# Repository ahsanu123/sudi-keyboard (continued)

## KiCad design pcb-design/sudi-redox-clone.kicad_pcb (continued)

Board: 2 copper layers, 145 parts (3 on the bottom side), 93 nets, no tracks yet.

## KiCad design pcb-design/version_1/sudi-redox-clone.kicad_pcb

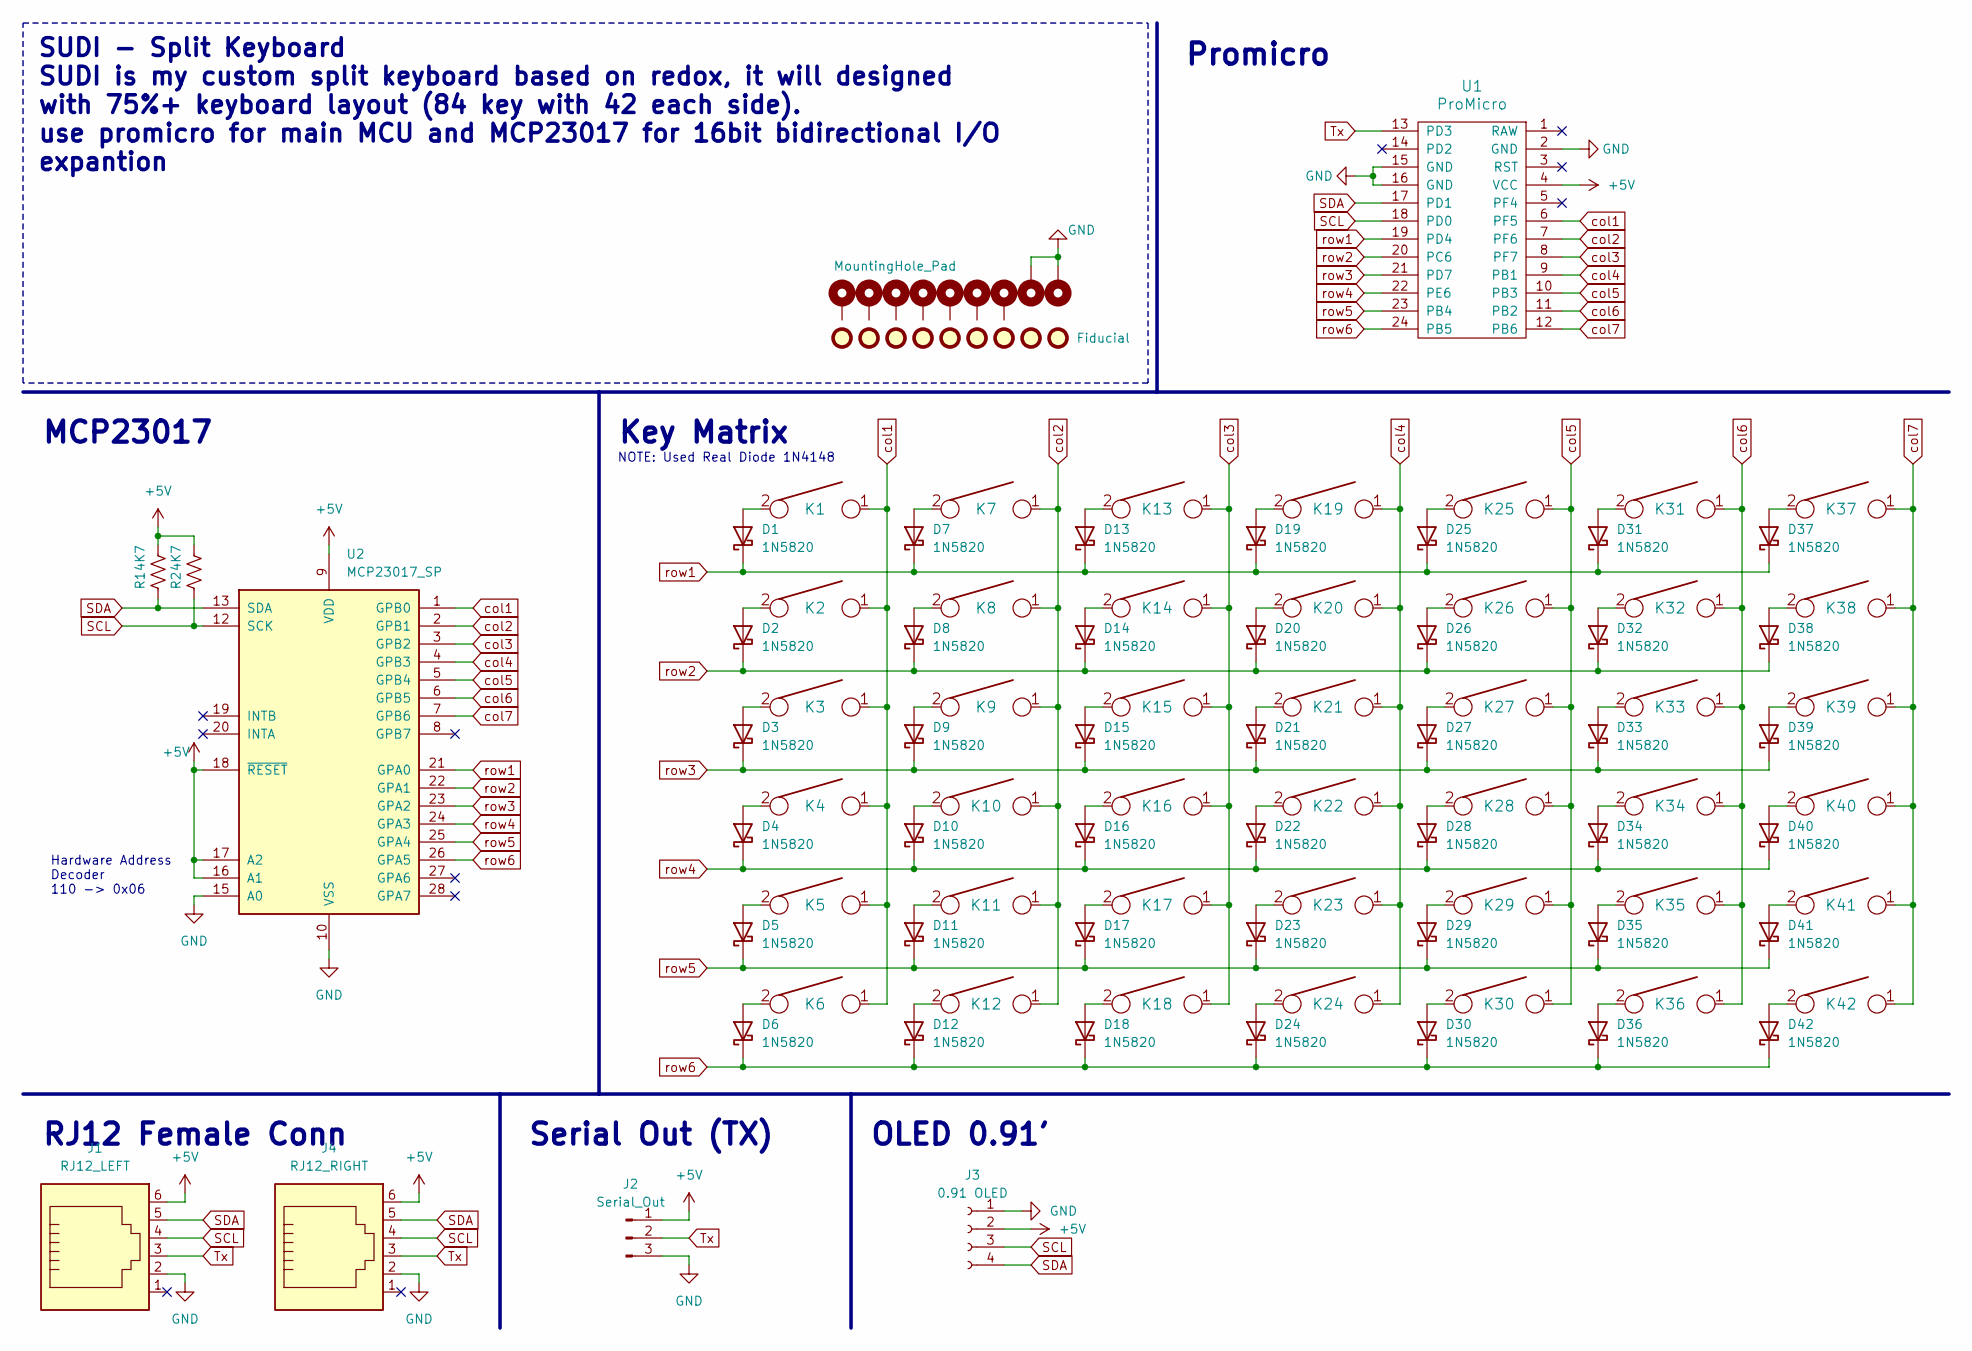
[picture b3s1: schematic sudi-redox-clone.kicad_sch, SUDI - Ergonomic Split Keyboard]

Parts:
D1, D2, D3, D4, D5, D6, D7, D8, D9, D10, D11, D12, D13, D14, D15, D16, D17, D18, D19, D20, D21, D22, D23, D24, D25, D26, D27, D28, D29, D30, D31, D32, D33, D34, D35, D36, D37, D38, D39, D40, D41, D42: 1N5820; D_SOD123_axial-dual
FID1, FID2, FID3, FID4, FID5, FID6, FID7, FID8, FID9: Fiducial; Fiducial_1mm_Mask3mm
H1, H2, H3, H4, H5, H6, H7, H8, H9: MountingHole_Pad; MountingHole_3.2mm_M3_DIN965_Pad
J1: RJ12_LEFT; RJ12_Amphenol_54601
J2: Serial_Out; PinHeader_1x03_P2.54mm_Horizontal
J3: 0.91 OLED; SSD1306-0.91-OLED-4pin-128x32
J4: RJ12_RIGHT; RJ12_Amphenol_54601
K1, K5, K6, K7, K8, K9, K10, K11, K12, K13, K14, K15, K16, K17, K18, K19, K20, K21, K22, K23, K24, K25, K26, K27, K28, K29, K30, K31, K32, K33, K34, K35, K36, K37, K38, K39, K40, K41, K42: KEYSW; Mx_Alps_100-dualside
K2, K3, K4: KEYSW; Mx_Alps_150-dualsided
R1, R2: 4K7; R_1206_3216Metric
U1: ProMicro; Pro_Micro
U2: MCP23017_SP; DIP-28_W7.62mm

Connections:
+5V: J1.6, J2.1, J3.2, J4.6, R1.1, R2.1, U1.4 (VCC), U2.9 (VDD), U2.16 (A1), U2.17 (A2), U2.18 (~RESET)
GND: H2.1, H9.1, J1.2, J2.3, J3.1, J4.2, U1.2 (GND), U1.15 (GND), U1.16 (GND), U2.10 (VSS), U2.15 (A0)
unnamed: D1.2 (A), K1.2
unnamed: D2.2 (A), K2.2
unnamed: D3.2 (A), K3.2
unnamed: D4.2 (A), K4.2
unnamed: D5.2 (A), K5.2
unnamed: D6.2 (A), K6.2
unnamed: D7.2 (A), K7.2
unnamed: D8.2 (A), K8.2
unnamed: D9.2 (A), K9.2
unnamed: D10.2 (A), K10.2
unnamed: D11.2 (A), K11.2
unnamed: D12.2 (A), K12.2
unnamed: D13.2 (A), K13.2
unnamed: D14.2 (A), K14.2
unnamed: D15.2 (A), K15.2
unnamed: D16.2 (A), K16.2
unnamed: D17.2 (A), K17.2
unnamed: D18.2 (A), K18.2
unnamed: D19.2 (A), K19.2
unnamed: D20.2 (A), K20.2
unnamed: D21.2 (A), K21.2
unnamed: D22.2 (A), K22.2
unnamed: D23.2 (A), K23.2
unnamed: D24.2 (A), K24.2
unnamed: D25.2 (A), K25.2
unnamed: D26.2 (A), K26.2
unnamed: D27.2 (A), K27.2
unnamed: D28.2 (A), K28.2
unnamed: D29.2 (A), K29.2
unnamed: D30.2 (A), K30.2
unnamed: D31.2 (A), K31.2
unnamed: D32.2 (A), K32.2
unnamed: D33.2 (A), K33.2
unnamed: D34.2 (A), K34.2
unnamed: D35.2 (A), K35.2
unnamed: D36.2 (A), K36.2
unnamed: D37.2 (A), K37.2
unnamed: D38.2 (A), K38.2
unnamed: D39.2 (A), K39.2
unnamed: D40.2 (A), K40.2
unnamed: D41.2 (A), K41.2
unnamed: D42.2 (A), K42.2
SCL: J1.4, J3.3, J4.4, R2.2, U1.18 (PD0), U2.12 (SCK)
SDA: J1.5, J3.4, J4.5, R1.2, U1.17 (PD1), U2.13 (SDA)
Tx: J1.3, J2.2, J4.3, U1.13 (PD3)
col1: K1.1, K2.1, K3.1, K4.1, K5.1, K6.1, U1.6 (PF5), U2.1 (GPB0)
col2: K7.1, K8.1, K9.1, K10.1, K11.1, K12.1, U1.7 (PF6), U2.2 (GPB1)
col3: K13.1, K14.1, K15.1, K16.1, K17.1, K18.1, U1.8 (PF7), U2.3 (GPB2)
col4: K19.1, K20.1, K21.1, K22.1, K23.1, K24.1, U1.9 (PB1), U2.4 (GPB3)
col5: K25.1, K26.1, K27.1, K28.1, K29.1, K30.1, U1.10 (PB3), U2.5 (GPB4)
col6: K31.1, K32.1, K33.1, K34.1, K35.1, K36.1, U1.11 (PB2), U2.6 (GPB5)
col7: K37.1, K38.1, K39.1, K40.1, K41.1, K42.1, U1.12 (PB6), U2.7 (GPB6)
row1: D1.1 (K), D7.1 (K), D13.1 (K), D19.1 (K), D25.1 (K), D31.1 (K), D37.1 (K), U1.19 (PD4), U2.21 (GPA0)
row2: D2.1 (K), D8.1 (K), D14.1 (K), D20.1 (K), D26.1 (K), D32.1 (K), D38.1 (K), U1.20 (PC6), U2.22 (GPA1)
row3: D3.1 (K), D9.1 (K), D15.1 (K), D21.1 (K), D27.1 (K), D33.1 (K), D39.1 (K), U1.21 (PD7), U2.23 (GPA2)
row4: D4.1 (K), D10.1 (K), D16.1 (K), D22.1 (K), D28.1 (K), D34.1 (K), D40.1 (K), U1.22 (PE6), U2.24 (GPA3)
row5: D5.1 (K), D11.1 (K), D17.1 (K), D23.1 (K), D29.1 (K), D35.1 (K), D41.1 (K), U1.23 (PB4), U2.25 (GPA4)
row6: D6.1 (K), D12.1 (K), D18.1 (K), D24.1 (K), D30.1 (K), D36.1 (K), D42.1 (K), U1.24 (PB5), U2.26 (GPA5)

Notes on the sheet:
SUDI - Split Keyboard SUDI is my custom split keyboard based on redox, it will designed with 75%+ keyboard layout (84 key with 42 each side). use promicro for main MCU and MCP23017 for 16bit bidirectional I/O expantion
Key Matrix
NOTE: Used Real Diode 1N4148
Serial Out (TX)
Hardware Address Decoder 110 -> 0x06
RJ12 Female Conn
OLED 0.91'
MCP23017
Promicro

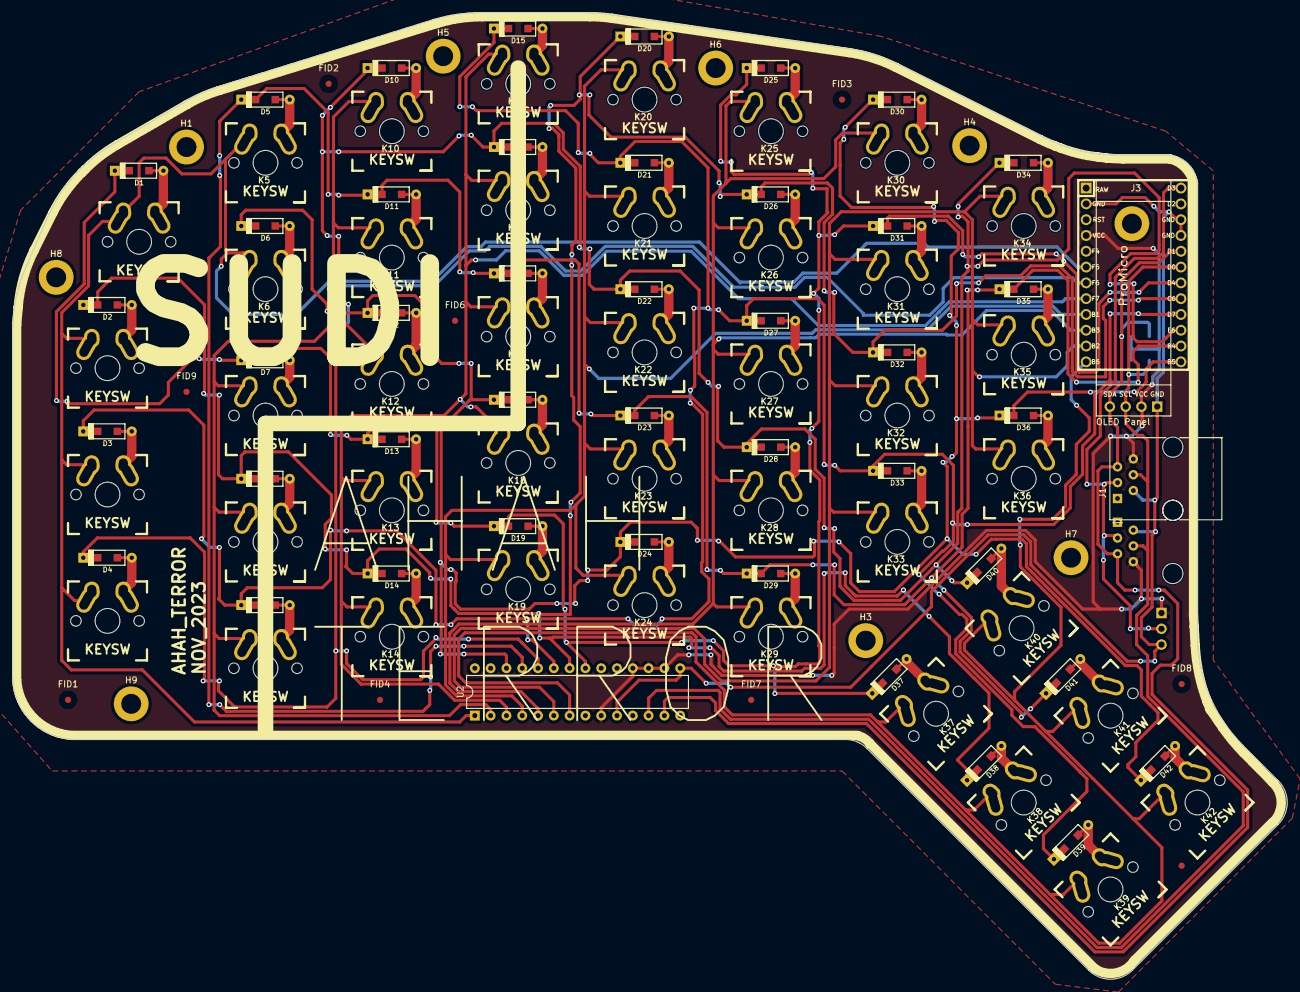
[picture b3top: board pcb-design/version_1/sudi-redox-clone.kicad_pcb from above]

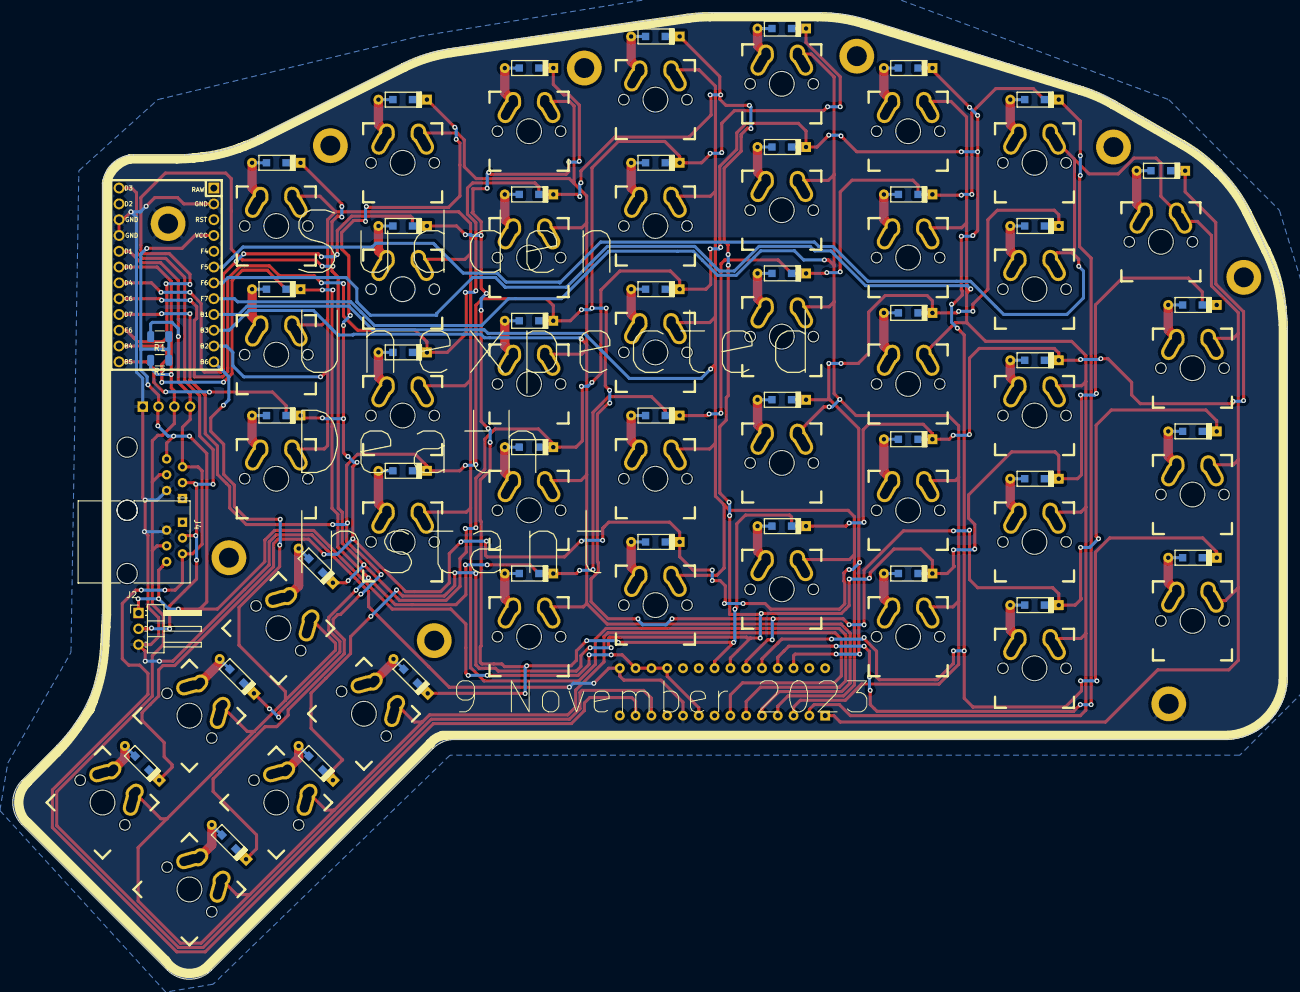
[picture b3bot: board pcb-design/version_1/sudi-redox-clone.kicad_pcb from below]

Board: 2 copper layers, 204.9 x 155.4 mm, 110 parts (4 on the bottom side), 60 nets.

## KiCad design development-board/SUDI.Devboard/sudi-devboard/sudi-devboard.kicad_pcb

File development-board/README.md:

## SUDI Development Board

Development board intended to understanding NRF52 nordic series for wireless keyboard, 
with Battery Management System (BMS), Bluetooth Low Energy Communication, USB, Vsense and 
LED Matrix.

## Description 

initial design decision, 

- NRF52820(5v tolerant, and USB, 256 kB flash, 32 kB RAM, QFN-40-EP(5x5), $2.6)
- NRF52832(**No** 5v tolerant, and **No** USB, 512/256 kB flash, 64/32 kB RAM, QFN-48-EP(6x6), $2.75)
- NRF52833QDXX(5v tolerant, and USB, 512 kB flash, 128 kB RAM, QFN-40-EP(5x5), $3.59)
- NRF52840(5v tolerant, and USB, 1 MB flash, 256 kB RAM, WLCSP-94(3.5x3.6) More difficult to Solder but most complete feature, $5.22)
- Add BMS into board 
- add IO expander, use MCP23017 smd
- board able to drive ws2812b (min voltage 3.5)
- vsense ic MAX17048
- switch to test 
- led for indicator 
- give all pin connector 
- usb with protection 
- uart 
- i2c 

## Note 

- [NRF51822 bluetooth module pin](https://quartzcomponents.com/cdn/shop/products/NRF51822-BLE-Module_1200x1200.jpg?v=1653290384)
  
```schell
left (from top perspectife, count from bottom)      Right (from top perspectife, count from bottom)  
PO3                                                 PO105                                            
PO4                                                 PO106                                            
PO1                                                 PO107                                            
PO2                                                 PO108                                            
PO30                                                PO109                                            
PO0                                                 PO110                                            
VDD                                                 PO111                                            
GND                                                 PO112                                            
PO28                                                PO003                                            
PO29                                                PO114                                            
NC                                                  PO015                                            
NC                                                  PO116                                            
PO24                                                SDA                                              
PO25                                                SCLK                                             
PO22                                                PO117                                            
PO23                                                PO119                                            
GND                                                 PO118                                            
PO21                                                PO200                                            

```

## Reference 

- [ebastler/zmk-designguide](https://github.com/ebastler/zmk-designguide)

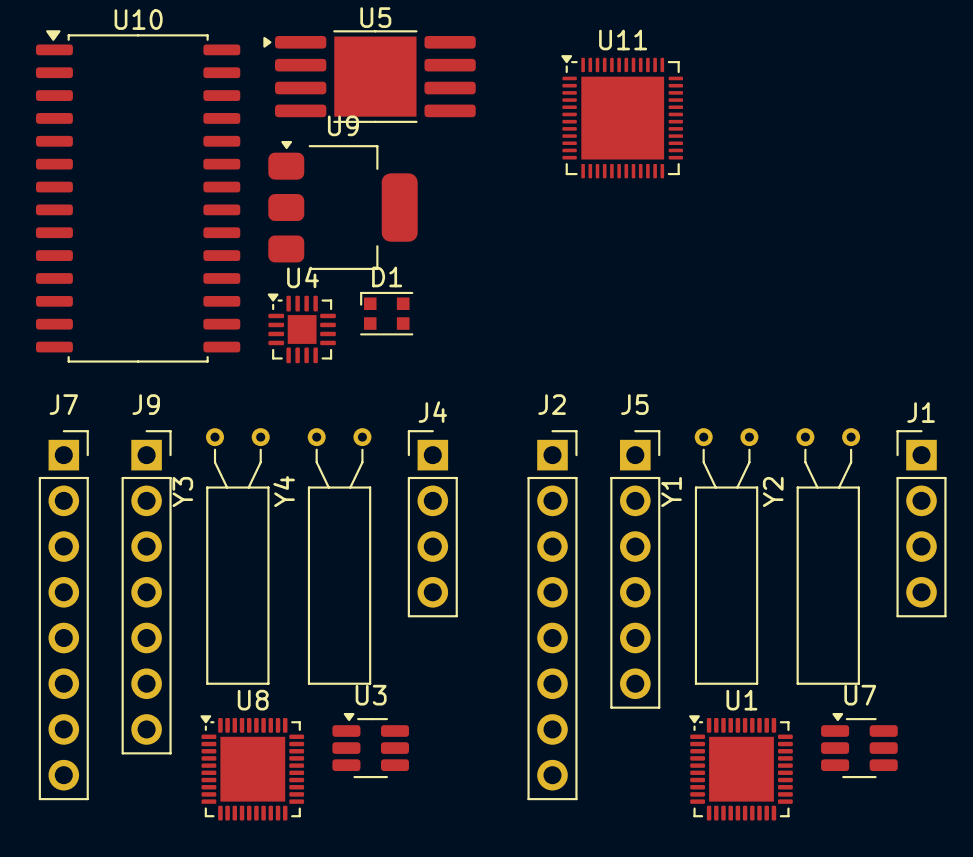
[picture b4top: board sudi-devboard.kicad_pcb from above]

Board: 2 copper layers, 20 parts (0 on the bottom side), 54 nets, no tracks yet.

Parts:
D1: WS2812B-2020; LED_WS2812B-2020_PLCC4_2.0x2.0mm
J1, J4: SWD_JLINK; PinHeader_1x04_P2.54mm_Vertical
J2, J7: Conn_01x08_Pin; PinSocket_1x08_P2.54mm_Vertical
J5: Conn_01x06_Pin; PinSocket_1x06_P2.54mm_Vertical
J9: Conn_01x07_Pin; PinSocket_1x07_P2.54mm_Vertical
U1: nRF52833_QDxx; QFN-40-1EP_5x5mm_P0.4mm_EP3.6x3.6mm
U3, U7: SRV05-4; SOT-23-6_Handsoldering
U4: BQ24075RGT; VQFN-16-1EP_3x3mm_P0.5mm_EP1.6x1.6mm
U5: TP4056; SOP-8-1EP_4.57x4.57mm_P1.27mm_EP4.57x4.45mm
U8: nRF52820-QDxx; QFN-40-1EP_5x5mm_P0.4mm_EP3.6x3.6mm
U9: AMS1117-3.3; SOT-223-3_TabPin2
U10: MCP23017_SO; SOIC-28W_7.5x17.9mm_P1.27mm
U11: nRF52832-QFxx; QFN-48-1EP_6x6mm_P0.4mm_EP4.6x4.6mm
Y1, Y3: 32Mhz; Crystal_AT310_D3.0mm_L10.0mm_Horizontal
Y2, Y4: 32.768kHz; Crystal_AT310_D3.0mm_L10.0mm_Horizontal

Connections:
/NRF52820/AIN0/P0.02: J7.1, U8.36 (AIN0/P0.02)
/NRF52820/AIN1/P0.03: J7.2, U8.35 (AIN1/P0.03)
/NRF52820/AIN2/P0.04: J7.3, U8.4 (AIN2/P0.04)
/NRF52820/AIN3/P0.05: J7.4, U8.5 (AIN3/P0.05)
/NRF52820/D+: U3.6 (IO4), U8.13 (D+)
/NRF52820/D-: U3.1 (IO1), U8.12 (D-)
/NRF52820/P0.06: J7.5, U8.6 (P0.06)
/NRF52820/P0.07: J7.6, U8.7 (P0.07)
/NRF52820/P0.08: J7.7, U8.31 (P0.08)
/NRF52820/P0.14: J7.8, U8.14 (P0.14)
/NRF52820/P0.15: J9.1, U8.15 (P0.15)
/NRF52820/P0.16: J9.2, U8.22 (P0.16)
/NRF52820/P0.17: J9.3, U8.23 (P0.17)
/NRF52820/P0.20: J9.4, U8.17 (P0.20)
/NRF52820/P0.28: J9.5, U8.34 (P0.28)
/NRF52820/P0.29: J9.6, U8.32 (P0.29)
/NRF52820/P0.30: J9.7, U8.33 (P0.30)
/NRF52820/SWDCLK: J4.2, U8.20 (SWDCLK)
/NRF52820/SWDIO: J4.3, U8.19 (SWDIO)
/NRF52820/XC1: U8.28 (XC1), Y3.1
/NRF52820/XC2: U8.29 (XC2), Y3.2
/NRF52820/XL1/P0.00: U8.2 (XL1/P0.00), Y4.1
/NRF52820/XL2/P0.01: U8.3 (XL2/P0.01), Y4.2
/NRF52833_QFN40/AIN0/P0.02: J2.1, U1.32 (AIN0/P0.02)
/NRF52833_QFN40/AIN1/P0.03: J2.2, U1.31 (AIN1/P0.03)
/NRF52833_QFN40/AIN2/P0.04: J2.3, U1.4 (AIN2/P0.04)
/NRF52833_QFN40/AIN3/P0.05: J2.4, U1.5 (AIN3/P0.05)
/NRF52833_QFN40/AIN4/P0.28: J5.3, U1.33 (AIN4/P0.28)
/NRF52833_QFN40/AIN5/P0.29: J5.4, U1.34 (AIN5/P0.29)
/NRF52833_QFN40/AIN6/P0.30: J5.5, U1.35 (AIN6/P0.30)
/NRF52833_QFN40/AIN7/P0.31: J5.6, U1.36 (AIN7/P0.31)
/NRF52833_QFN40/D+: U1.13 (D+), U7.6 (IO4)
/NRF52833_QFN40/D-: U1.12 (D-), U7.1 (IO1)
/NRF52833_QFN40/NFC1/P0.09: J2.5, U1.22 (NFC1/P0.09)
/NRF52833_QFN40/NFC2/P0.10: J2.6, U1.23 (NFC2/P0.10)
/NRF52833_QFN40/P0.11: J2.7, U1.7 (P0.11)
/NRF52833_QFN40/P0.15: J2.8, U1.14 (P0.15)
/NRF52833_QFN40/P0.17: J5.1, U1.15 (P0.17)
/NRF52833_QFN40/P0.20: J5.2, U1.17 (P0.20)
/NRF52833_QFN40/SWDCLK: J1.2, U1.20 (SWDCLK)
/NRF52833_QFN40/SWDIO: J1.3, U1.19 (SWDIO)
/NRF52833_QFN40/XC1: U1.28 (XC1), Y1.1
/NRF52833_QFN40/XC2: U1.29 (XC2), Y1.2
/NRF52833_QFN40/XL1/P0.00: U1.2 (XL1/P0.00), Y2.1
/NRF52833_QFN40/XL2/P0.01: U1.3 (XL2/P0.01), Y2.2
GND: J1.1, J4.1, U1.25 (VSS_PA), U1.37 (VSS), U1.41 (VSS), U3.2 (VN), U7.2 (VN), U8.25 (VSS_PA), U8.37 (VSS), U8.41 (VSS)
unnamed: U1.26 (DEC6), U1.38 (DEC4)
unnamed: U4.2 (BAT), U4.3 (BAT)
unnamed: U4.10 (OUT), U4.11 (OUT)
unnamed: U4.8 (VSS), U4.17 (VSS)
unnamed: U11.13 (VDD), U11.36 (VDD), U11.48 (VDD)
unnamed: U11.31 (VSS), U11.45 (VSS), U11.49 (VSS)
VBUS: U1.9 (VDDH), U1.10 (VBUS), U3.5 (VP), U7.5 (VP)
VDD: J1.4, J4.4, U1.8 (VDD), U1.18 (VDD), U1.30 (VDD), U1.40 (VDD)

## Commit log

2023-11-04 create schematic
2023-11-04 rename folder from sudi-redox-clone to pcb-design
2023-11-08 generate gerber and routed board rev 0.1
2023-11-12 adding firmware from symlink
2023-11-18 generate dxf file - 1
2023-11-18 generate stepfile - 1
2023-11-19 add keycap cut guide - 1
2023-11-30 physical keyboard made with revision - see nb
2023-12-16 keyboard functionality has working, need a fix on mechanical casing
    in this commit keyboard has programmed tested on linux pc and windows pc.
    qmk use info.json for generate keyboard layout and automatic generate default_keyboard.h.
2023-12-16 add eticatted schematic
2023-12-16 add banner image
2023-12-21 add casing to repo
2024-06-28 [jumat 28 juni 2024] sudi v2 started
2024-07-01 add canadian library to repo
2024-07-01 updatee
2024-07-02 add several component to schematic
2024-07-06 add nordic design Reference
2024-07-07 [minggu 7 juli 7:27] create receiver schematic
2024-07-07 [minggu 7 juli 8:55] cleaning schematic layout
2024-07-07 [minggu 7 juli 12:12] create pcb cut profile
2024-07-07 [minggu 7 juli 19:32] finish PCB Layout
2024-07-10 add some route progress
2024-07-10 update some route
2024-07-17 [rabu 17 juli 19:13] update route progress
2024-07-24 [rabu 24 juli 20:17] finish keyboard layout - todo receiver
2024-07-24 update image
2024-07-24 whoami
2024-07-31 finsihed receiver route
2024-08-04 update firmware to version 2 use nrf51 sdk
2024-08-07 cmake/makefile builded but fail to link
2024-08-07 nrf51 target compiled with cmake script
2024-08-08 jlink debugging worked
2024-08-11 update nrf5
2024-08-11 finally fucking blinking nrf51822 working
2024-08-24 update from linux
2024-08-25 add zephyr
2024-08-25 backu
2024-08-25 add sudi-v2 zephyr project structure
2024-08-25 add device tree references
2024-09-04 change NRF51822 into NRF52832
2024-09-05 updateRoute to use NRF52832
2024-09-05 add CH340C
2024-09-07 zephyr blinky example worked on NRF51822XXAA
2024-09-09 west.tml (manifest) is use to enable some module in zephyr
2024-11-01 [11-01-1954] add test point into NRF
2024-11-12 [11-13-0459] add svg and switch to schematic
2024-11-14 [14-11-2129] init SUDI development board
    nit
2024-11-16 [16-11-1807] change chargin mechanism
2024-11-16 [16-11-1807] add capacitor to WS2812C-2020
    change gif
2024-11-17 [17-11-1825] tweak values and silkscreen
    nit, add pdf
    nit
    nit schematic
    add svg
2024-11-20 [20-11-2007] create LCSC Cart from BOM
2024-12-14 [12-13-2203] combine wired version 1 with version 2
2024-12-14 [12-13-2203] combine wired version 1 with version 2
    Update README.md
    Update README_V1.md
    update license
    Create LICENSE
2024-12-15 [12-15-1122] add NRF51822 Module Folder
    update readme to include official bluetooth learning resource
    add docs
    update readme
    Update README.md
    add zephyr submodule for learning it
2024-12-15 [12-15-1955] add basic custom configuration based on NRF51822
2024-12-16 [12-16-2150] add capacitor to anntena
    renamed kicad project
2025-01-19 [01-19-2213] generate gerber and order pcb
2025-02-08 [02-08-1952] Ordering Component From LCSC
2025-02-09 [02-09-2215] Start to create Casing Design In Creo
2025-05-01 [02-09-2215] Start to create Casing Design In Creo
    Update README.md
    Update README.md
2025-05-01 [05-01-0821] rechecking casing enclosure
2025-05-09 [05-09-1013] gerber is not up to date, there is short circuit between 3.3 and gnd
2025-05-09 [05-09-2033] able to flash and build rmk example, need to deep dive into rmk keyboard repository
2025-05-10 [05-09-2035] delete gerber and un-needed file from version 2 folder
2025-05-11 [05-11-0854] adding note to rmk firmware
    Update README.md
    Update README.md
    Update README.md
2025-05-12 [05-12-0740] adding sudi firmware project
2025-05-12 [05-12-1100] first try to read direct pin matrix worked
    nit
2025-05-12 [05-12-0850] change structure
2025-05-12 [05-12-1109] cleanup v2 zmk and v2 nordic native
2025-05-12 [05-12-1200] move direct pin reader in its own struct
2025-05-12 [05-12-1224] before think about passing into next middleware
2025-05-13 [05-12-1755] inductor in sepic 5v is burnout :(
    Update README.md
    Update README.md
    Update README.md
2025-05-19 [05-20-0528] add basic note to run usbipd on wsl
    nit
2025-05-25 [05-20-0528] add basic note to run usbipd on wsl
    nit
    Update README.md
2025-05-25 [05-25-1535] trying to run basic battery services, no luck
2025-05-25 [05-25-1901] add bleak to reading battery service, work but mostly intermitent
    Update README.md
    Update README.md
2025-08-23 feat(doc): add log of learning ble
2025-08-23 feat(component): change component to correct size
2025-08-23 chore: add file WSL
2025-08-24 chore(poc): add test to running ble_bas_peripheral from trouble example
2025-08-24 feat(test): add test to advertise as hid keyboard
2025-08-25 chore(doc): add refernce doc about bluetooth architecture
2025-08-25 feat: add 'minions' small version of sudi v2
2025-08-27 feat: add compiled hex into v1
2025-08-28 feat: routing minions part 1
2025-08-30 feat: finish routing part 1
2025-08-30 feat: add fabrication file
2025-08-30 feat: fabricate first minions pcb, its going well
2025-09-01 feat: add no_std test in host pc
2025-10-11 feat: add coretan
2025-10-12 feat: create merge_2_matrix
2025-10-19 feat: attempt to create fsm executor
2025-10-19 feat(test): basic test event loop work
2025-10-19 feat: create hold oneclick transition send idle
2026-02-06 feat: init really basic shared firmware library project
2026-03-16 chore: delete gcode and fabrication output
